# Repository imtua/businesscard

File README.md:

# NFC Card Remastered - Hacker Card

<a href="github.com/imtua/nfc-card-remastered"><b>NFC Card Remastered</b></a> is a digital NFC business card that features a LED in it. The copper ring or the NFC antennas actually harvest a little amount of electricity through the antenna from the phone or the device and with that harvested electricity, the LED lights up. How cool is that!

I made this as a reference/example card for <a href="jams.hackclub.com/jam/hacker-card"><b>Hacker Card</b></a>, a program where you can learn how to make your own hacker card and get it for free. It contains an implementation of **Near Field Communication (NFC) technology**.

**Terms:**
- **Electricity:** Discovered over thousands of years through observations of static electricity and lightning, with foundational principles of **electromagnetic induction** discovered by **Michael Faraday** in **1831**.

- **NFC (Near Field Communication):** A modern wireless communication standard created in 2002 that uses **magnetic field induction** to power tiny passive microchips just enough to exchange data.

That's how **NFC Tags** harvest tiny amounts of energy from a device, and with that, we'll light an LED in it!

## Features:
- Runs on **NFC** technology.
- Can store little data in it.
- Can light up an integrated LED through harvesting electricity.
- Cool design! (More cooler than <a href="github.com/imtua/ImtCard"><b>ImtCard</b></a>)

## Schematics

## PCB

## 3D Overview

# Color Inspos

# Conclusion
You can actually get inspired from my project and try it yourself. This is made on KiCad so it provides:
* **businesscard.kicad_sch** file
* **businesscard.kicad_pcb** file

With these, you can do it yourself. Other than that, if you want to order exactly one like me, find this file-
* **gerber.zip**

Stardance Project Link: <a href="https://stardance.hackclub.com/projects/59907"><b>NFC CARD REMASTERED</b></a>

Made by <a href="github.com/imtua"><b>Imtiaz Ahamed</b></a> with the help of <a href="hackclub.com"><b>Hack Club</b></a>

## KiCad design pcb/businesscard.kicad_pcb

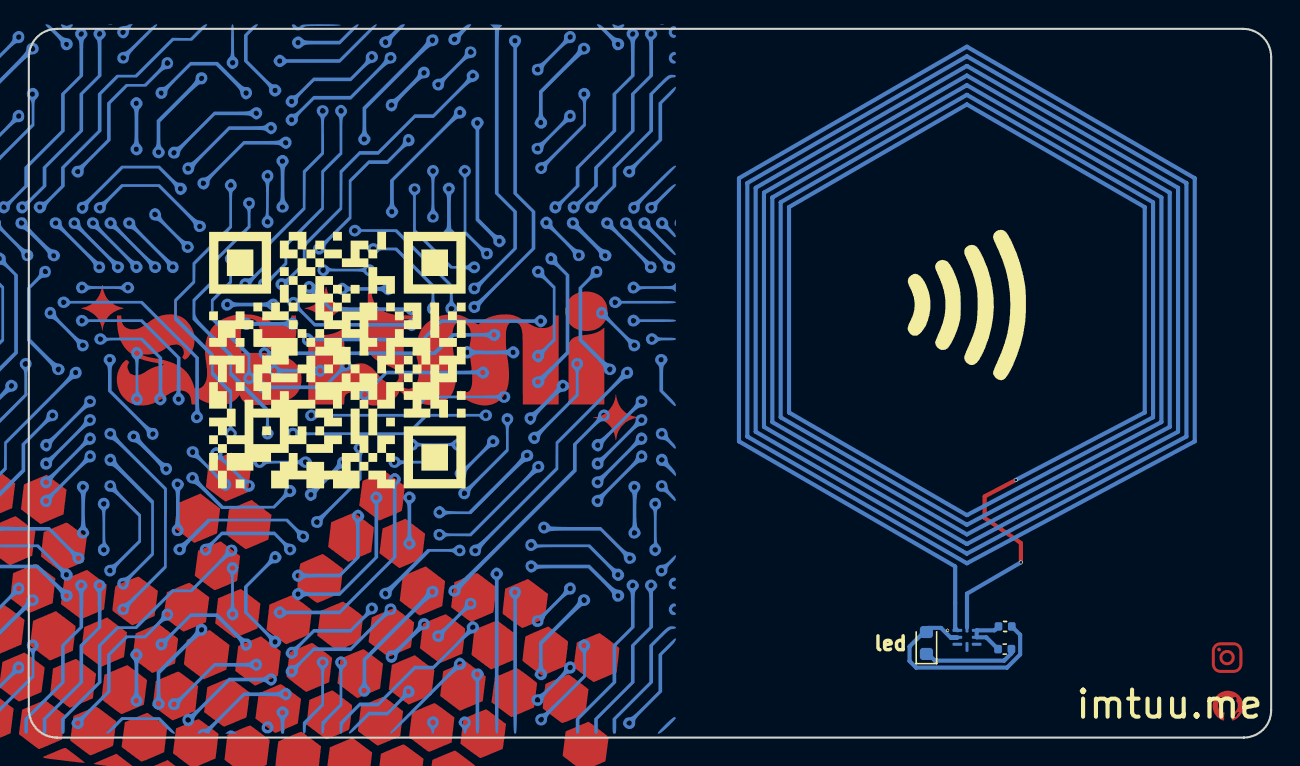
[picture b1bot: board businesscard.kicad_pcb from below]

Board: 2 copper layers, 89.4 x 51.0 mm, 4 parts (4 on the bottom side), 3 nets.

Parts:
C1: 220nF; C_0402_1005Metric
D1: LED_0603_1608Metric
R1: 47ohm; C_0402_1005Metric
U1: NT3H1101; QFN8P50_160X160X50L40X20N

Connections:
unnamed: D1.1, R1.2
unnamed: C1.2, D1.2, U1.2 (VSS)
unnamed: C1.1, R1.1, U1.6 (VCC), U1.7 (VOUT)

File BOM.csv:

"Id";"Designator";"Footprint";"Quantity";"Designation";"Supplier and ref";
1;"C1";"C_0402_1005Metric";1;"220nF";;;
2;"D1";"LED_0603_1608Metric";1;"LED_0603_1608Metric";;;
3;"R1";"C_0402_1005Metric";1;"47ohm";;;
4;"U1";"QFN8P50_160X160X50L40X20N";1;"NT3H1101";;;
